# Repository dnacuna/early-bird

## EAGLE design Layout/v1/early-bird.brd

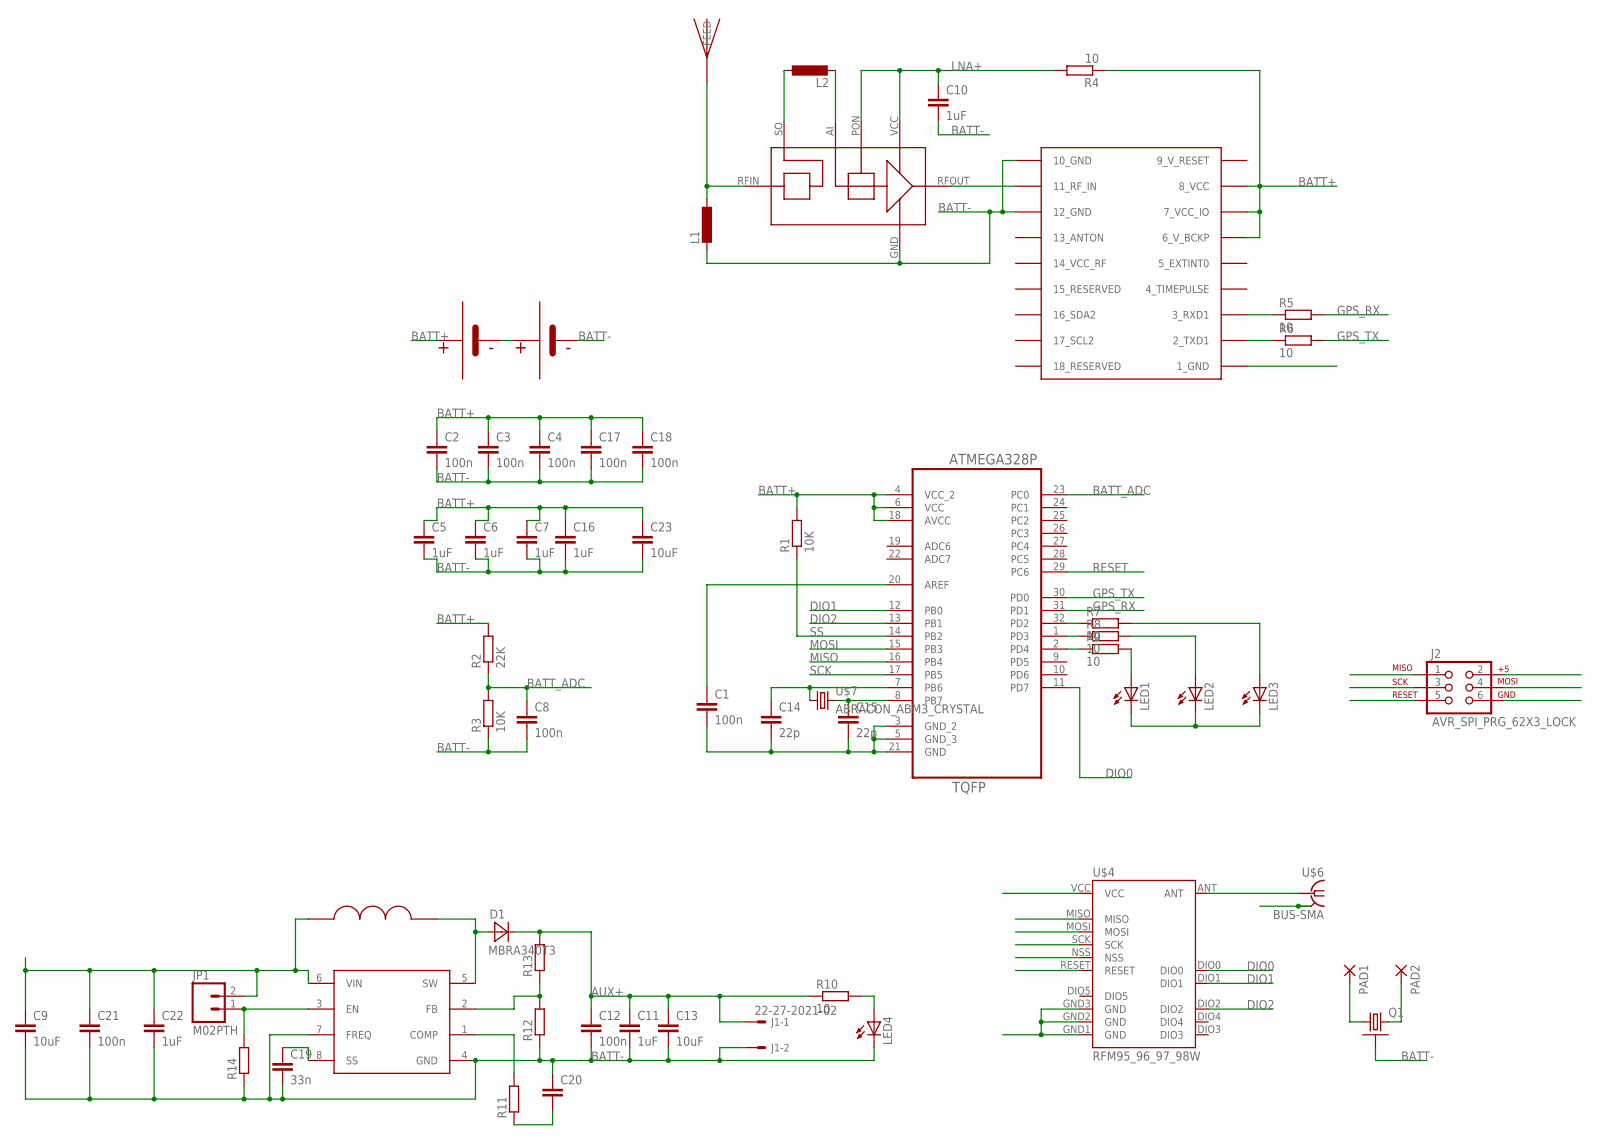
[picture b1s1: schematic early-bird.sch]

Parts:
C1, C2, C3, C4, C8, C12, C17, C18, C21: 100n; C0402
C5, C6, C7, C10, C11, C16, C22: 1uF; C0603
C9, C13, C23: 10uF; C1210
C14, C15: 22p; C0402
C19: 33n; C0402
C20: C-EUC0402; C0402
D1: MBRA340T3; SMA
J1: 22-27-2021-02; 6410-02
J2: AVR_SPI_PRG_62X3_LOCK; 2X3_LOCK
JP1: M02PTH; 1X02
L1, L2: L-EUL2012C; L2012C
LED1, LED2, LED3, LED4: LEDCHIPLED_1206; CHIPLED_1206
PAD1, PAD2: SMD2; SMD1,27-2,54
Q1: CRYSTALCTS406; CTS406
R1, R3: 10K; R0402
R2: 22K; R0402
R4, R5, R6, R7, R8, R9, R10: 10; R0402
R11, R12, R13, R14: R-EU_R0402; R0402
U1: ATMEGA328P-AU; QFP80P900X900X120-32N
U$1, U$2: KEYSTONE-92-AA-BATTERY-HOLDER; KEYSTONE-92-AA-BATTERY
U$3: JTI_ANTENNA-1575AT43A40
U$4: RFM95_96_97_98W
U$5: UBLOX_MAX
U$6: BUS-SMA
U$7: ABRACON_ABM3_CRYSTAL
U$8: ADP1612; SOP65P490X110-8N
U$9: BGM1034N7; TSNP-7-10
U$10: MULTICOMP_8MM_INDUCTOR; 8MM_SQ_INDUCTOR

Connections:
9_V_RESET: U$5.9_V_RESET
AUX+: C11.1, C12.1, C13.1, D1.C, J1.1, R10.1, R13.2
BATT+: C2.1, C3.1, C4.1, C5.1, C6.1, C7.1, C9.1, C16.1, C17.1, C18.1, C21.1, C22.1, C23.1, J2.2, JP1.2, R1.2, R2.2, R4.1, U1.4 (VCC_2), U1.6 (VCC), U1.18 (AVCC), U$1.VBATT (BATT+), U$1.VBATT1 (BATT+), U$4.VCC, U$5.6_V_BCKP, U$5.7_VCC_IO, U$5.8_VCC, U$8.6 (VIN), U$10.P$2
BATT-: C1.2, C2.2, C3.2, C4.2, C5.2, C6.2, C7.2, C8.2, C9.2, C10.2, C11.2, C12.2, C13.2, C14.2, C15.2, C16.2, C17.2, C18.2, C19.2, C20.1, C21.2, C22.2, C23.2, J1.2, J2.6, L1.2, LED1.C, LED2.C, LED3.C, LED4.C, Q1.2, Q1.4, R3.1, R12.1, R14.1, U1.3 (GND_2), U1.5 (GND_3), U1.21 (GND), U$2.GND (BATT-), U$2.GND2 (BATT-), U$4.GND1 (GND), U$4.GND2 (GND), U$4.GND3 (GND), U$5.1_GND, U$5.10_GND, U$5.12_GND, U$6.2 (GND), U$6.3 (GND), U$6.4 (GND), U$6.5 (GND), U$8.4 (GND), U$8.7 (FREQ), U$9.GND
BATT_ADC: C8.1, R2.1, R3.2, U1.23 (PC0)
DIO0: U1.11 (PD7), U$4.DIO0
DIO1: U1.12 (PB0), U$4.DIO1
DIO2: U1.13 (PB1), U$4.DIO2
GPS_RX: R5.2, U1.31 (PD1)
GPS_TX: R6.2, U1.30 (PD0)
LNA+: C10.1, R4.2, U$9.PON, U$9.VCC
MISO: J2.1, U1.16 (PB4), U$4.MISO
MOSI: J2.4, U1.15 (PB3), U$4.MOSI
unnamed: U$4.ANT, U$6.1
unnamed: L1.1, U$3.FEED, U$9.RFIN
unnamed: LED3.A, R7.2
unnamed: LED2.A, R8.2
unnamed: C20.2, R11.1
unnamed: R5.1, U$5.3_RXD1
unnamed: R6.1, U$5.2_TXD1
unnamed: C1.1, U1.20 (AREF)
unnamed: JP1.1, R14.2, U$8.3 (EN)
unnamed: R7.1, U1.32 (PD2)
unnamed: L2.1, U$9.SO
unnamed: R8.1, U1.1 (PD3)
unnamed: R9.1, U1.2 (PD4)
unnamed: LED1.A, R9.2
unnamed: LED4.A, R10.2
unnamed: U$1.GND (BATT-), U$1.GND2 (BATT-), U$2.VBATT (BATT+), U$2.VBATT1 (BATT+)
unnamed: C15.1, U1.8 (PB7), U$7.P$2 (2)
unnamed: C14.1, U1.7 (PB6), U$7.P$1 (1)
unnamed: C19.1, U$8.8 (SS)
unnamed: R11.2, U$8.1 (COMP)
unnamed: R12.2, R13.1, U$8.2 (FB)
unnamed: PAD1.1, Q1.1
unnamed: D1.A, U$8.5 (SW), U$10.P$1
unnamed: L2.2, U$9.AI
unnamed: U$5.11_RF_IN, U$9.RFOUT
unnamed: PAD2.1, Q1.3 (2)
RADIO_RESET: U$4.RESET
RESET: J2.5, U1.29 (PC6)
SCK: J2.3, U1.17 (PB5), U$4.SCK
SS: R1.1, U1.14 (PB2), U$4.NSS

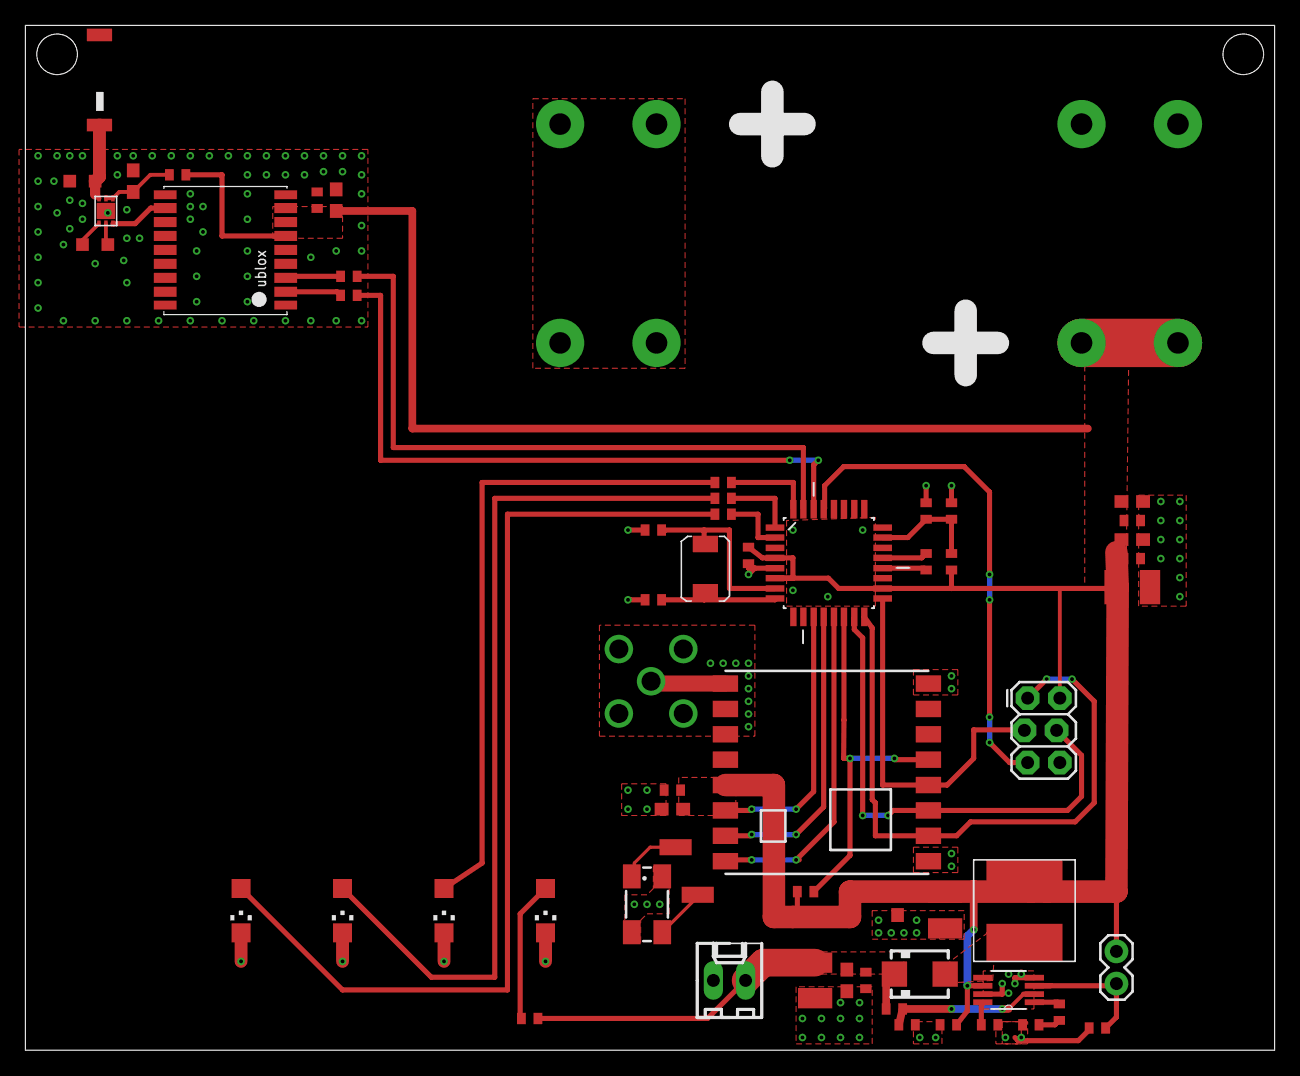
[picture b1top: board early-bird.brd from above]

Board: 2 copper layers, 98.5 x 80.8 mm, 61 parts (0 on the bottom side), 41 nets.

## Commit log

2014-11-23 Add files to git.
2014-12-23 Add PCB progress.
2014-12-24 Layout Progress, redraw schematic a little.
2014-12-25 Add CAM file.
2014-12-25 Stage for fab?
2014-12-25 Fix CAM file.
2014-12-25 Remove renderings.
2014-12-25 Final tweaks..
2014-12-25 More Final tweaks..
2014-12-25 Reduce via size to 0.3mm
2014-12-25 Tweak sma ground polygon.
2014-12-25 Add gerber files.
2014-12-27 Add Battery SCAD file.
2014-12-28 Update silkscreen.
2015-01-08 Add STL file.
2015-01-08 Add SoMakeIt Slicer configs.
2015-01-08 Add v1 gcode output.
2015-01-12 Add Battery v1 render.
2015-01-13 Remove gcode renders.
2015-01-13 Add lulzbot configs.
2015-01-13 Remove old png render.
2015-01-13 Battery CAD: Update dimensions.
2015-01-13 Battery CAD: Render latest gcodes for all printers.
2015-01-13 Modify fast config for slower perimeter and less infill (10%)
2015-01-13 Render gcode with slow perimeter, less infill.
2015-01-16 Add image render.

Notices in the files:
parts and their libraries:
SparkFun-Connectors: Licensing: Creative Commons ShareAlike 4.0 International - https://creativecommons.org/licenses/by-sa/4.0
